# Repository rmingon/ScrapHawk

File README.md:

# ScrapHawk

*Ultra-budget, high-performance RP2040 flight controller stack bypassing expensive legacy silicon.*

## The Concept: Rethinking the Flight Controller

For years, custom flight controllers have relied on expensive, legacy single-core silicon. ScrapHawk takes a radically different approach. By utilizing the ultra-affordable Raspberry Pi RP2040, modern FreeRTOS Symmetric Multiprocessing (SMP), and hardware-level Programmable I/O (PIO), ScrapHawk delivers a zero-latency, high-performance flight stack on a hacker's budget.

Beyond the silicon, ScrapHawk solves one of the most frustrating problems in drone engineering: Electromagnetic Interference (EMI) from high-current motor ESCs disrupting sensitive navigation sensors. 

To combat this, the ScrapHawk architecture is physically decoupled into two separate printed circuit boards connected by a 6-pin JST-SH (1.0mm) umbilical cable.

---

## Software Architecture: Multi-Core RTOS & PIO Offloading

The RP2040 features dual Cortex-M0+ cores. Instead of treating this as a generic processing pool, ScrapHawk leverages FreeRTOS SMP to rigidly enforce core affinity, completely decoupling the real-time flight dynamics from slower, blocking navigation tasks.

### PIO: Zero-Latency Motor Control
Traditionally, generating DSHOT signals for ESCs requires complex timer/DMA configurations that eat up CPU cycles. ScrapHawk completely bypasses the CPU for motor control. By mapping the motor output pins to the RP2040's hardware PIO state machines, the DSHOT timing is handled independently at the hardware level. Core 0 simply pushes throttle values into a FIFO buffer, and the PIO hardware seamlessly clocks out the precise DSHOT pulses.

---

## Hardware Architecture: Split-Board Design

### Board 1: Main FC (The Brain & Muscle)

This is the core flight management and power delivery board, situated in the center of the drone frame.
* **MCU:** Raspberry Pi RP2040 (QFN-56) paired with 16MB QSPI Flash (Winbond W25Q128JVSIQ).
* **IMU:** STMicroelectronics LSM6DS3TR-C, placed precisely at the physical center of the PCB for accurate rotational data. Routed via SPI0 with Data Ready Interrupts.
* **Power Delivery:** A robust dual-stage filter ensures clean power despite ESC noise. A massive 470uF 35V Low-ESR input capacitor feeds a 5V Buck Converter (MP1584EN, 10uH inductor), which then feeds a 3.3V LDO (AMS1117-3.3).
* **Motor & Receiver I/O:** 4 corner ESC solder pads driven by PIO (GPIO 10-13), plus a dedicated 4-pin header for ExpressLRS 2.4GHz receivers via UART1.
* **Connectivity:** USB-C with proper dual 5.1kΩ pull-downs and 27Ω D+/D- series resistors. 
* **The Umbilical:** A 6-pin right-angle SMD connector carrying 5V, GND, UART0 (for GPS), and I2C0 (for Compass). It crucially includes 2.2kΩ pull-up resistors on the I2C lines to maintain signal integrity over the physical wire capacitance.

### Board 2: Nav Puck (The Senses)

Designed to be mounted high on a mast, this board keeps the magnetometer and GPS completely isolated from the EMI generated by the motors and power leads.
* **Clean Local Power:** Receives 5V from the umbilical, which is filtered again through a localized AMS1117-3.3 LDO to provide exceptionally clean power exclusively for the sensors.
* **GPS:** Zhongke Micro ATGM336H-5N (UART) equipped with a U.FL connector for an active ceramic patch antenna. It includes an onboard MS621FE 3V backup battery to retain ephemeris data for instant hot-starts.
* **Compass:** QST QMC5883L (I2C) for precise, noise-free heading data.

---

## Who is this for?
ScrapHawk is designed for drone hardware hackers, custom flight controller developers, and FreeRTOS engineers who want to explore modern RTOS paradigms and PIO capabilities without being locked into expensive, proprietary, or legacy ecosystems. It proves that with clever software engineering and thoughtful hardware isolation, cheap silicon can fly just as well—if not better—than the expensive alternatives.

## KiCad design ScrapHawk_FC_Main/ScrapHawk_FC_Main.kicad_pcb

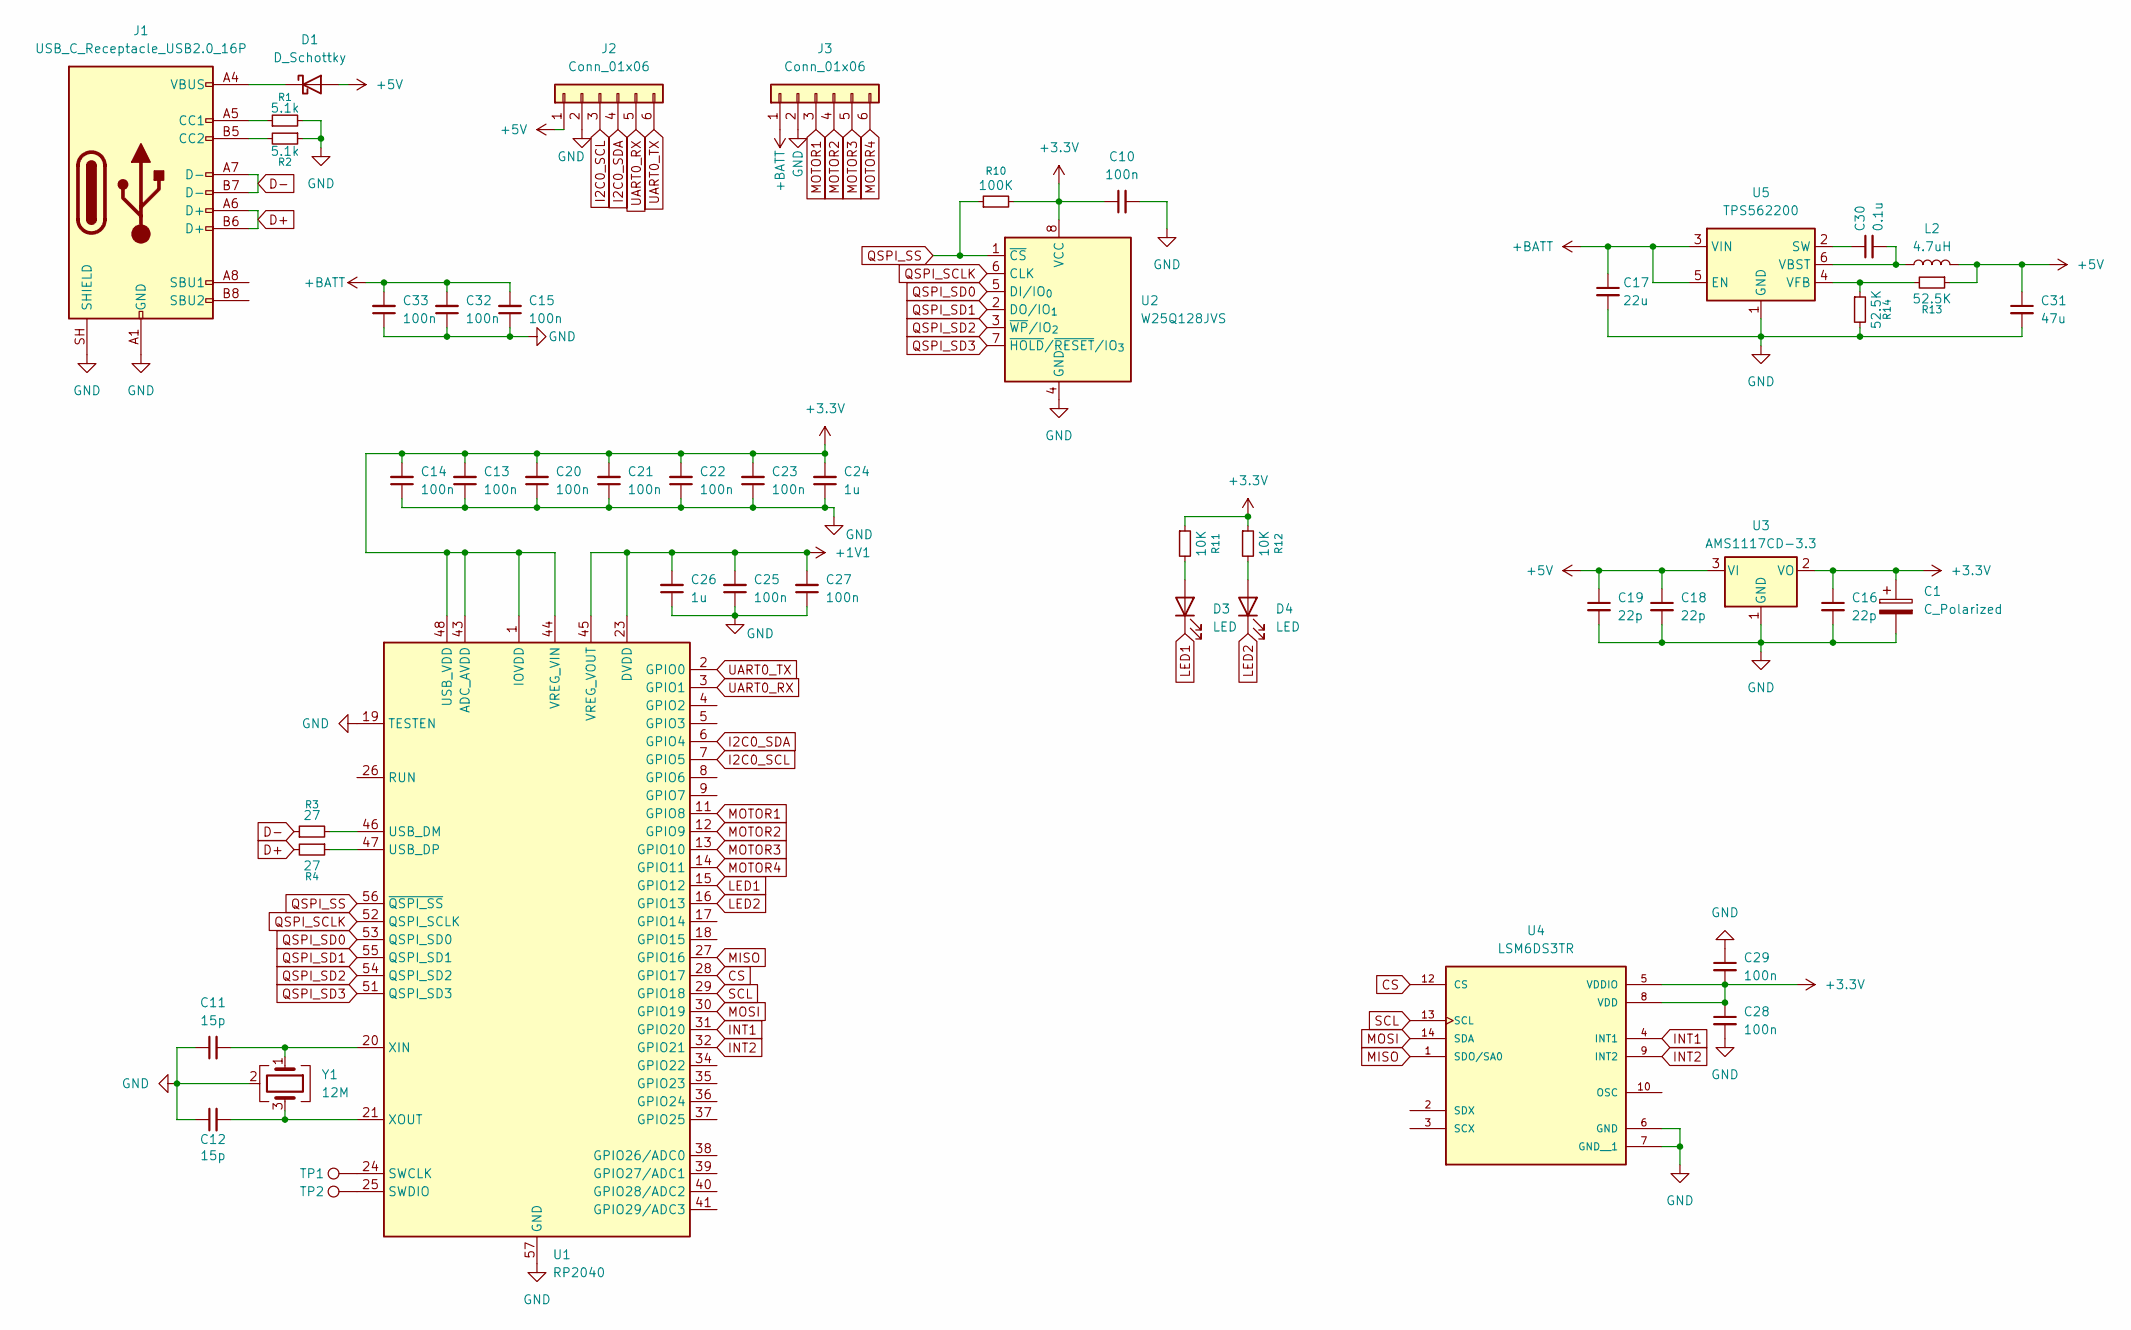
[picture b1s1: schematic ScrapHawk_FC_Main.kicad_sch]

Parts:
C1: C_Polarized; CP_Elec_6.3x5.2
C10, C13, C14, C20, C21, C22, C23, C25, C27, C28, C29: 100n; C_0603_1608Metric
C11, C12: 15p; C_0603_1608Metric
C15, C32, C33: 100n; C_1206_3216Metric
C16, C18, C19: 22p; C_0603_1608Metric
C17: 22u; C_0603_1608Metric
C24, C26: 1u; C_0603_1608Metric
C30: 0.1u; C_0603_1608Metric
C31: 47u; C_0603_1608Metric
D1: D_Schottky; D_0805_2012Metric
D3, D4: LED; C_0603_1608Metric
J1: USB_C_Receptacle_USB2.0_16P; USB_C_Receptacle_G-Switch_GT-USB-7010ASV
J2, J3: Conn_01x06; JST_SH_BM06B-SRSS-TB_1x06-1MP_P1.00mm_Vertical
L2: 4.7uH; L_Chilisin_BMRA00050520
R1, R2: 5.1k; R_0603_1608Metric
R3, R4: 27; R_0603_1608Metric
R10: 100K; R_0603_1608Metric
R11, R12: 10K; R_0603_1608Metric
R13, R14: 52.5K; R_0603_1608Metric
TP1, TP2: TestPoint; TestPoint_Pad_D1.5mm
U1: RP2040; QFN-56-1EP_7x7mm_P0.4mm_EP3.2x3.2mm
U2: W25Q128JVS; SOIC-8_5.3x5.3mm_P1.27mm
U3: AMS1117CD-3.3; SOT-223
U4: LSM6DS3TR; PQFN50P300X250X86-14N; PARTREV 2
U5: TPS562200; SOT-23-6
Y1: 12M; Crystal_SMD_SeikoEpson_TSX3225-4Pin_3.2x2.5mm

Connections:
+1V1: C25.2, C26.2, C27.2, U1.23 (DVDD), U1.45 (VREG_VOUT), U1.50 (DVDD)
+3.3V: C1.1, C10.1, C13.2, C14.2, C16.1, C20.2, C21.2, C22.2, C23.2, C24.2, C28.1, C29.2, R10.2, R11.1, R12.1, U1.1 (IOVDD), U1.10 (IOVDD), U1.22 (IOVDD), U1.33 (IOVDD), U1.42 (IOVDD), U1.43 (ADC_AVDD), U1.44 (VREG_VIN), U1.48 (USB_VDD), U1.49 (IOVDD), U2.8 (VCC), U3.2 (VO), U4.5 (VDDIO), U4.8 (VDD)
+5V: C18.1, C19.1, C31.1, D1.2 (A), J2.1, L2.2, R13.1, U3.3 (VI)
+BATT: C15.2, C17.1, C32.2, C33.2, J3.1, U5.3 (VIN), U5.5 (EN)
CS: U1.28 (GPIO17), U4.12 (CS)
D+: J1.A6 (D+), J1.B6 (D+), R4.2
D-: J1.A7 (D-), J1.B7 (D-), R3.1
GND: C1.2, C10.2, C11.1, C12.1, C13.1, C14.1, C15.1, C16.2, C17.2, C18.2, C19.2, C20.1, C21.1, C22.1, C23.1, C24.1, C25.1, C26.1, C27.1, C28.2, C29.1, C31.2, C32.1, C33.1, J1.A1 (GND), J1.A12 (GND), J1.B1 (GND), J1.B12 (GND), J1.SH (SHIELD), J2.2, J3.2, R1.2, R2.1, R14.2, U1.19 (TESTEN), U1.57 (GND), U2.4 (GND), U3.1 (GND), U4.6 (GND), U4.7 (GND__1), U5.1 (GND), Y1.2 (G), Y1.4 (G)
I2C0_SCL: J2.3, U1.7 (GPIO5)
I2C0_SDA: J2.4, U1.6 (GPIO4)
INT1: U1.31 (GPIO20), U4.4 (INT1)
INT2: U1.32 (GPIO21), U4.9 (INT2)
LED1: D3.1 (K), U1.15 (GPIO12)
LED2: D4.1 (K), U1.16 (GPIO13)
MISO: U1.27 (GPIO16), U4.1 (SDO/SA0)
MOSI: U1.30 (GPIO19), U4.14 (SDA)
MOTOR1: J3.3, U1.11 (GPIO8)
MOTOR2: J3.4, U1.12 (GPIO9)
MOTOR3: J3.5, U1.13 (GPIO10)
MOTOR4: J3.6, U1.14 (GPIO11)
unnamed: D1.1 (K), J1.A4 (VBUS), J1.A9 (VBUS), J1.B4 (VBUS), J1.B9 (VBUS)
unnamed: D3.2 (A), R11.2
unnamed: D4.2 (A), R12.2
unnamed: J1.A5 (CC1), R1.1
unnamed: J1.B5 (CC2), R2.2
unnamed: TP1.1 (1_1), U1.24 (SWCLK)
unnamed: TP2.1 (1_1), U1.25 (SWDIO)
unnamed: R3.2, U1.46 (USB_DM)
unnamed: R4.1, U1.47 (USB_DP)
unnamed: C11.2, U1.20 (XIN), Y1.1
unnamed: C12.2, U1.21 (XOUT), Y1.3
unnamed: C30.1, U5.2 (SW)
unnamed: C30.2, L2.1, U5.6 (VBST)
unnamed: R13.2, R14.1, U5.4 (VFB)
QSPI_SCLK: U1.52 (QSPI_SCLK), U2.6 (CLK)
QSPI_SD0: U1.53 (QSPI_SD0), U2.5 (DI/IO_{0})
QSPI_SD1: U1.55 (QSPI_SD1), U2.2 (DO/IO_{1})
QSPI_SD2: U1.54 (QSPI_SD2), U2.3 (~WP/IO_{2})
QSPI_SD3: U1.51 (QSPI_SD3), U2.7 (~HOLD/~RESET/IO_{3})
QSPI_SS: R10.1, U1.56 (~QSPI_SS), U2.1 (~CS)
SCL: U1.29 (GPIO18), U4.13 (SCL)
UART0_RX: J2.5, U1.3 (GPIO1)
UART0_TX: J2.6, U1.2 (GPIO0)

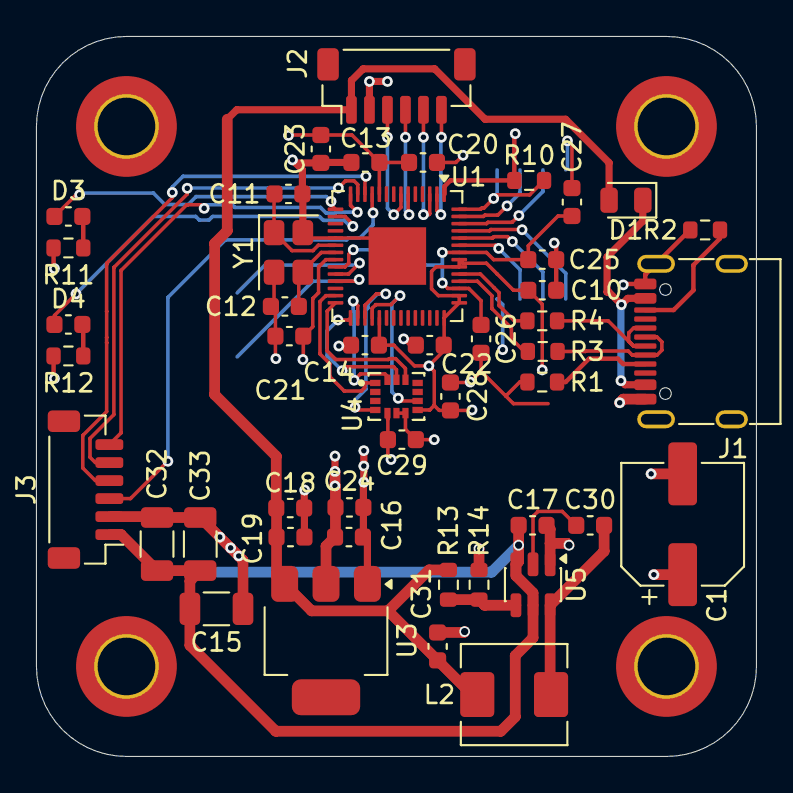
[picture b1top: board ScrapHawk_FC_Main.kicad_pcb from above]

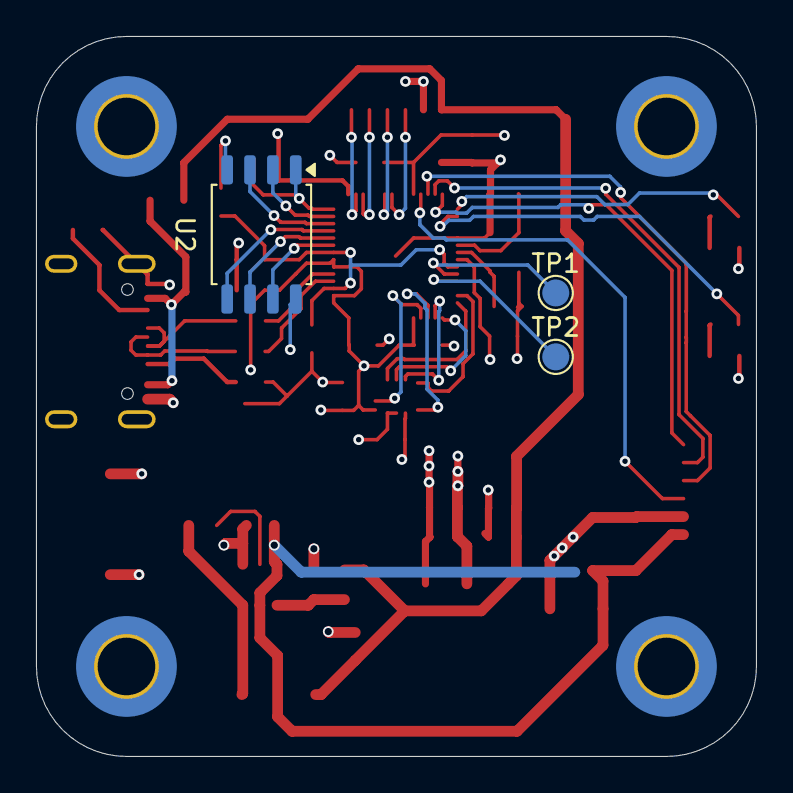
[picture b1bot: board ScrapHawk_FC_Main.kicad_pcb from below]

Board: 4 copper layers, 40.0 x 40.0 mm, 49 parts (3 on the bottom side), 43 nets.

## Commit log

2026-04-19 add kicad ignore files
2026-04-19 add flash - rp2040 wire
2026-04-19 add step down + usb c connector wire
2026-04-19 update gyro
2026-04-20 wire pcb place components
2026-04-26 finish pcb wiring
2026-04-26 fix capacitors size
2026-04-26 update capacitor
2026-04-26 add pictures
2026-04-26 add readme
2026-04-29 update stepdown
2026-04-29 update decoupling capacitor battery
